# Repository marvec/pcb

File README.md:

pcb
===

Circuit boards for KiCAD

relay-board - I2C based relay board that can control 8 AC outputs (250V 10A)

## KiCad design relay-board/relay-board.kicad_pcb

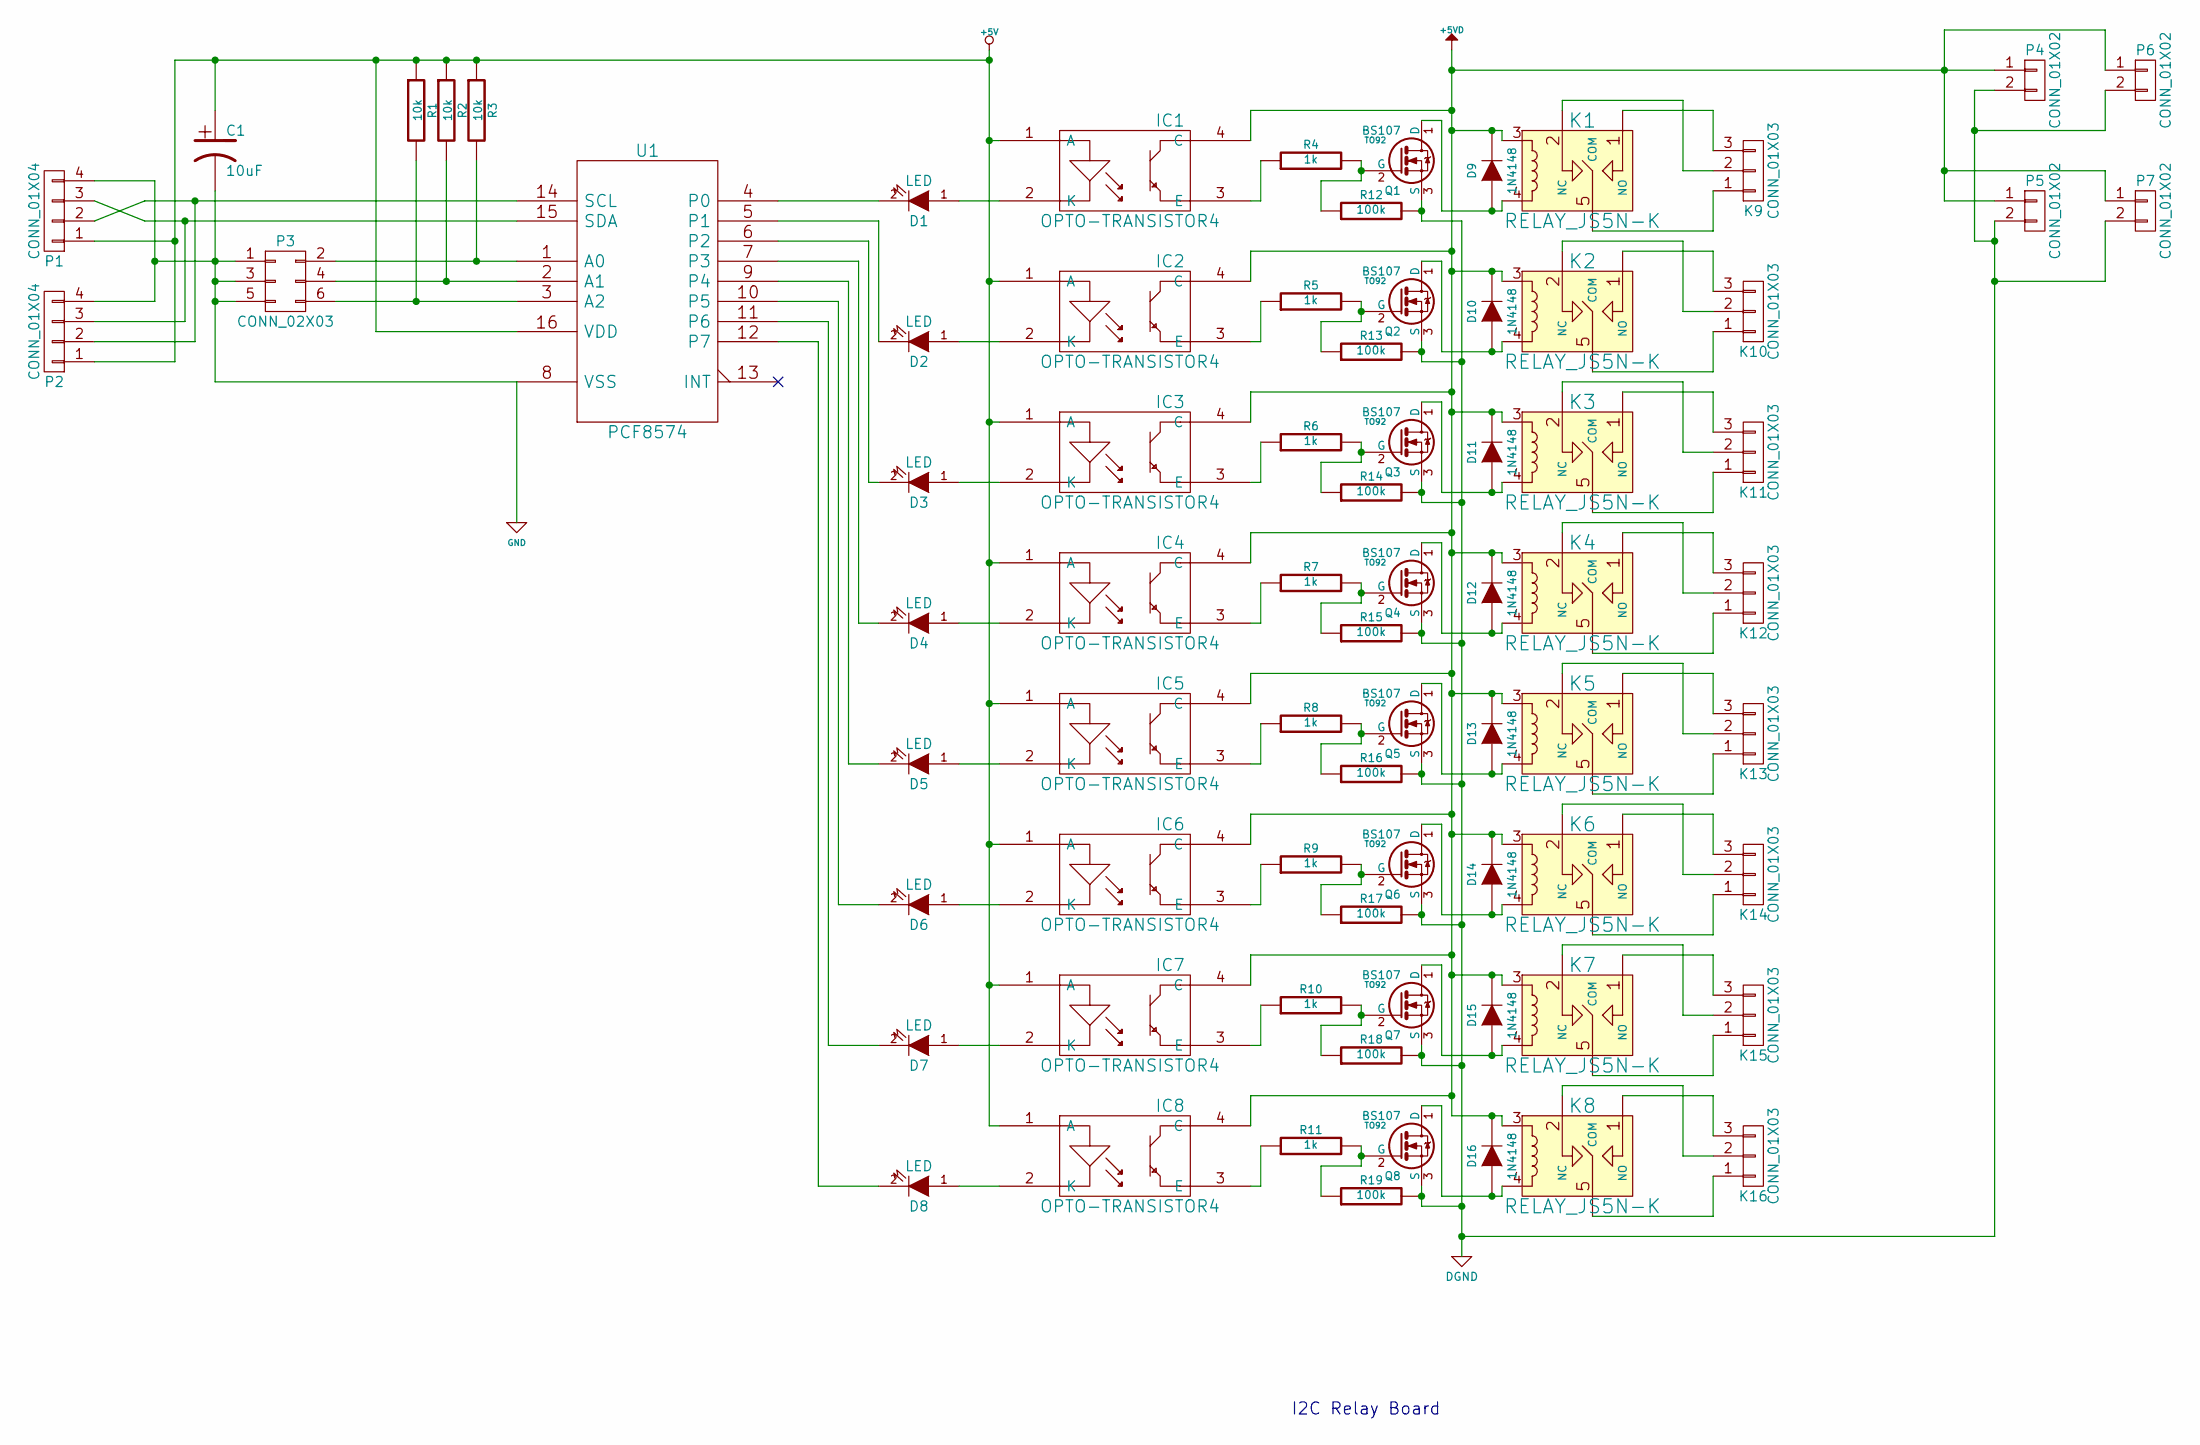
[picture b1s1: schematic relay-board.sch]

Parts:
C1: 10uF
D1, D2, D3, D4, D5, D6, D7, D8: LED
D9, D10, D11, D12, D13, D14, D15, D16: 1N4148
IC1, IC2, IC3, IC4, IC5, IC6, IC7, IC8: OPTO-TRANSISTOR4
K1, K2, K3, K4, K5, K6, K7, K8: RELAY_JS5N-K
K9, K10, K11, K12, K13, K14, K15, K16: CONN_01X03
P1, P2: CONN_01X04
P3: CONN_02X03
P4, P5, P6, P7: CONN_01X02
Q1, Q2, Q3, Q4, Q5, Q6, Q7, Q8: BS107; TO92
R1, R2, R3: 10k
R4, R5, R6, R7, R8, R9, R10, R11: 1k
R12, R13, R14, R15, R16, R17, R18, R19: 100k
U1: PCF8574

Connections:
+5V: C1.1, IC1.1 (A), IC2.1 (A), IC3.1 (A), IC4.1 (A), IC5.1 (A), IC6.1 (A), IC7.1 (A), IC8.1 (A), P1.1, P2.1, R1.1, R2.1, R3.1, U1.16 (VDD)
+5VD: D9.2 (K), D10.2 (K), D11.2 (K), D12.2 (K), D13.2 (K), D14.2 (K), D15.2 (K), D16.2 (K), IC1.4 (C), IC2.4 (C), IC3.4 (C), IC4.4 (C), IC5.4 (C), IC6.4 (C), IC7.4 (C), IC8.4 (C), K1.3, K2.3, K3.3, K4.3, K5.3, K6.3, K7.3, K8.3, P4.1, P5.1, P6.1, P7.1
DGND: P4.2, P5.2, P6.2, P7.2, Q1.3 (S), Q2.3 (S), Q3.3 (S), Q4.3 (S), Q5.3 (S), Q6.3 (S), Q7.3 (S), Q8.3 (S), R12.2, R13.2, R14.2, R15.2, R16.2, R17.2, R18.2, R19.2
GND: C1.2, P1.4, P2.4, P3.1, P3.3, P3.5, U1.8 (VSS)
unnamed: IC6.3 (E), R9.1
unnamed: IC7.3 (E), R10.1
unnamed: K7.5 (COM), K15.1
unnamed: K7.2 (NC), K15.2
unnamed: K8.5 (COM), K16.1
unnamed: IC8.3 (E), R11.1
unnamed: K8.2 (NC), K16.2
unnamed: IC4.3 (E), R7.1
unnamed: K5.2 (NC), K13.2
unnamed: K5.5 (COM), K13.1
unnamed: K4.5 (COM), K12.1
unnamed: K4.2 (NC), K12.2
unnamed: IC3.3 (E), R6.1
unnamed: K6.5 (COM), K14.1
unnamed: K6.2 (NC), K14.2
unnamed: IC5.3 (E), R8.1
unnamed: K6.1 (NO), K14.3
unnamed: K5.1 (NO), K13.3
unnamed: K1.1 (NO), K9.3
unnamed: K1.2 (NC), K9.2
unnamed: K1.5 (COM), K9.1
unnamed: K2.5 (COM), K10.1
unnamed: K3.5 (COM), K11.1
unnamed: K7.1 (NO), K15.3
unnamed: K8.1 (NO), K16.3
unnamed: K3.2 (NC), K11.2
unnamed: K2.1 (NO), K10.3
unnamed: K2.2 (NC), K10.2
unnamed: K3.1 (NO), K11.3
unnamed: K4.1 (NO), K12.3
unnamed: IC2.3 (E), R5.1
unnamed: IC1.3 (E), R4.1
unnamed: D2.1 (A), IC2.2 (K)
unnamed: D3.2 (K), U1.6 (P2)
unnamed: D4.2 (K), U1.7 (P3)
unnamed: D4.1 (A), IC4.2 (K)
unnamed: D2.2 (K), U1.5 (P1)
unnamed: D6.2 (K), U1.10 (P5)
unnamed: D5.2 (K), U1.9 (P4)
unnamed: D1.2 (K), U1.4 (P0)
unnamed: P1.2, P2.2, U1.14 (SCL)
unnamed: P1.3, P2.3, U1.15 (SDA)
unnamed: D8.1 (A), IC8.2 (K)
unnamed: D3.1 (A), IC3.2 (K)
unnamed: D5.1 (A), IC5.2 (K)
unnamed: D7.2 (K), U1.11 (P6)
unnamed: D8.2 (K), U1.12 (P7)
unnamed: D6.1 (A), IC6.2 (K)
unnamed: D7.1 (A), IC7.2 (K)
unnamed: D1.1 (A), IC1.2 (K)
unnamed: Q6.2 (G), R9.2, R17.1
unnamed: Q7.2 (G), R10.2, R18.1
unnamed: Q5.2 (G), R8.2, R16.1
unnamed: D10.1 (A), K2.4, Q2.1 (D)
unnamed: D11.1 (A), K3.4, Q3.1 (D)
unnamed: D12.1 (A), K4.4, Q4.1 (D)
unnamed: D13.1 (A), K5.4, Q5.1 (D)
unnamed: D14.1 (A), K6.4, Q6.1 (D)
unnamed: D15.1 (A), K7.4, Q7.1 (D)
unnamed: D16.1 (A), K8.4, Q8.1 (D)
unnamed: Q8.2 (G), R11.2, R19.1
unnamed: D9.1 (A), K1.4, Q1.1 (D)
unnamed: Q1.2 (G), R4.2, R12.1
unnamed: Q3.2 (G), R6.2, R14.1
unnamed: Q4.2 (G), R7.2, R15.1
unnamed: Q2.2 (G), R5.2, R13.1
unnamed: P3.6, R1.2, U1.3 (A2)
unnamed: P3.2, R3.2, U1.1 (A0)
unnamed: P3.4, R2.2, U1.2 (A1)

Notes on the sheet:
I2C Relay Board

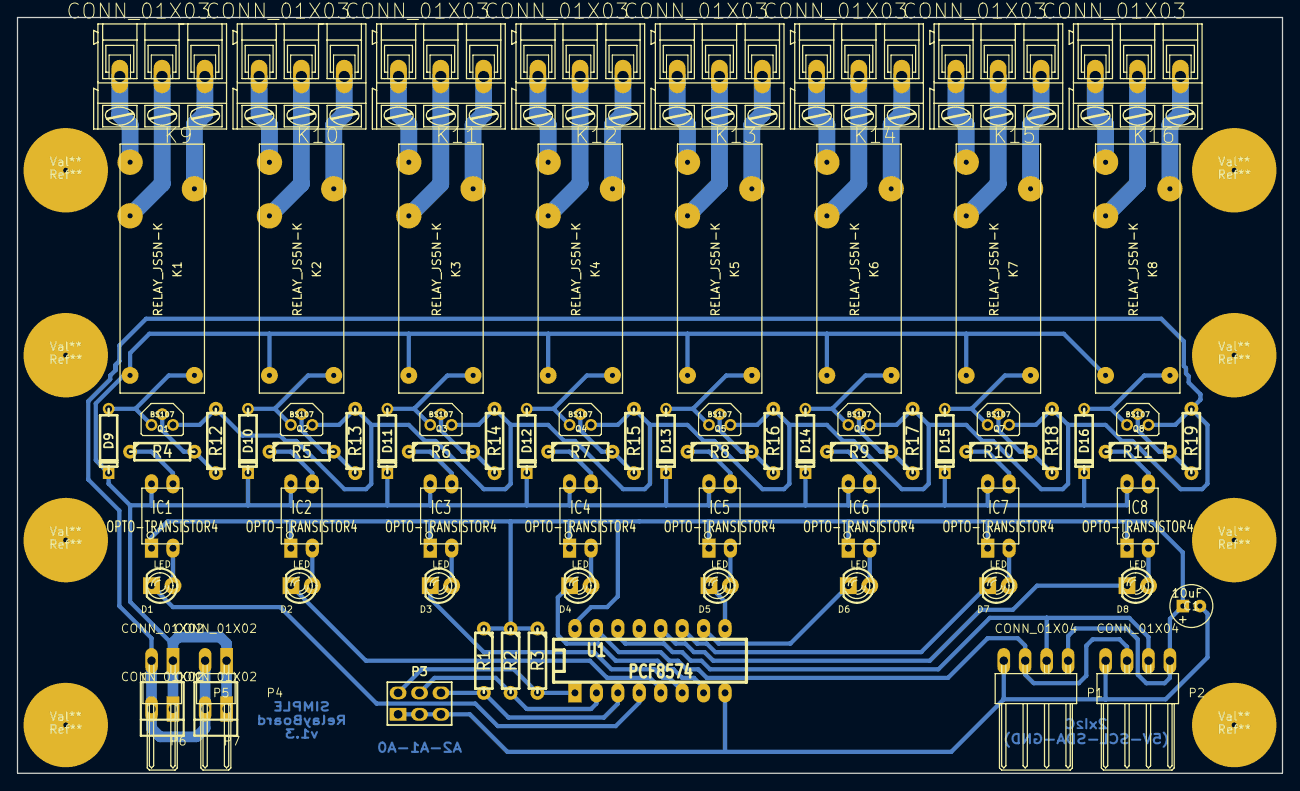
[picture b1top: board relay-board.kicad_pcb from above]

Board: 2 copper layers, 149.9 x 89.5 mm, 84 parts (0 on the bottom side), 73 nets.

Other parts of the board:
Ref**: Val**; screw-pad
Ref**#2, Ref**#3, Ref**#4, Ref**#5, Ref**#6, Ref**#7, Ref**#8: Val**; screw-pad

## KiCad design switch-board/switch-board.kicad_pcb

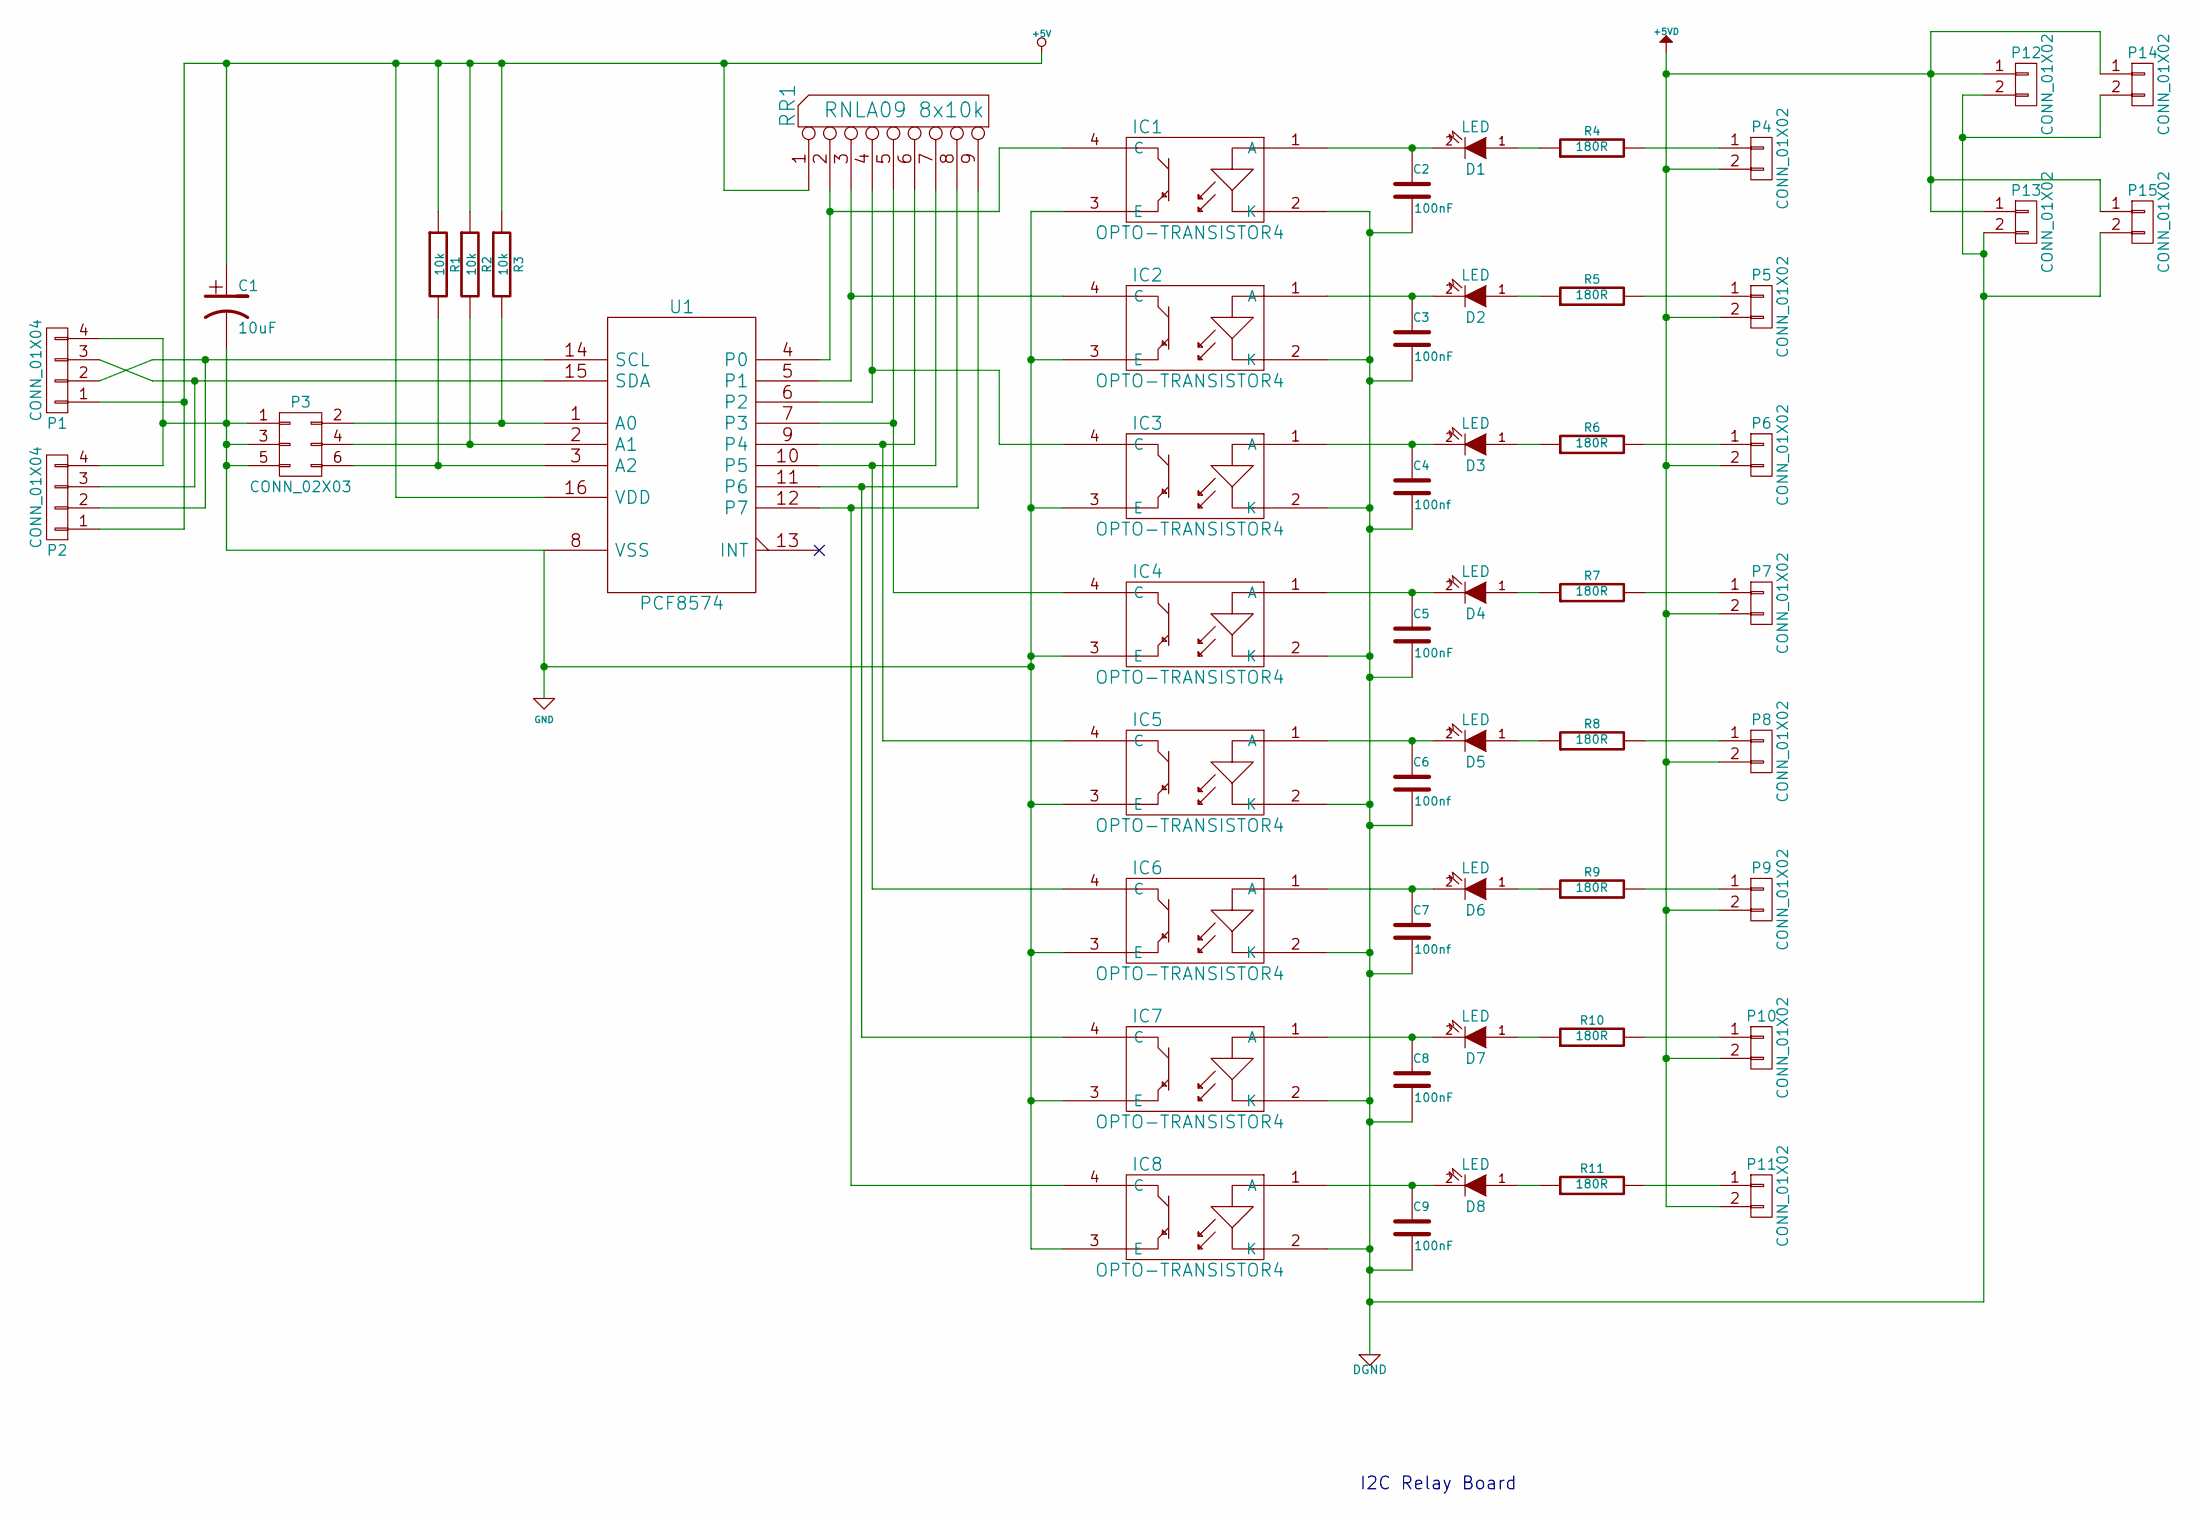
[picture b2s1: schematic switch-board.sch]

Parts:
C1: 10uF
C2, C3, C5, C8, C9: 100nF
C4, C6, C7: 100nf
D1, D2, D3, D4, D5, D6, D7, D8: LED
IC1, IC2, IC3, IC4, IC5, IC6, IC7, IC8: OPTO-TRANSISTOR4
P1, P2: CONN_01X04
P3: CONN_02X03
P4, P5, P6, P7, P8, P9, P10, P11, P12, P13, P14, P15: CONN_01X02
R1, R2, R3: 10k
R4, R5, R6, R7, R8, R9, R10, R11: 180R
RR1: RNLA09 8x10k
U1: PCF8574

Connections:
+5V: C1.1, P1.1, P2.1, R1.1, R2.1, R3.1, RR1.1 (COM), U1.16 (VDD)
+5VD: P4.2, P5.2, P6.2, P7.2, P8.2, P9.2, P10.2, P11.2, P12.1, P13.1, P14.1, P15.1
DGND: C2.2, C3.2, C4.2, C5.2, C6.2, C7.2, C8.2, C9.2, IC1.2 (K), IC2.2 (K), IC3.2 (K), IC4.2 (K), IC5.2 (K), IC6.2 (K), IC7.2 (K), IC8.2 (K), P12.2, P13.2, P14.2, P15.2
GND: C1.2, IC1.3 (E), IC2.3 (E), IC3.3 (E), IC4.3 (E), IC5.3 (E), IC6.3 (E), IC7.3 (E), IC8.3 (E), P1.4, P2.4, P3.1, P3.3, P3.5, U1.8 (VSS)
unnamed: D7.1 (A), R10.1
unnamed: P9.1, R9.2
unnamed: P8.1, R8.2
unnamed: P7.1, R7.2
unnamed: P6.1, R6.2
unnamed: P5.1, R5.2
unnamed: P4.1, R4.2
unnamed: D1.1 (A), R4.1
unnamed: P10.1, R10.2
unnamed: P3.4, R2.2, U1.2 (A1)
unnamed: P3.6, R1.2, U1.3 (A2)
unnamed: P3.2, R3.2, U1.1 (A0)
unnamed: P11.1, R11.2
unnamed: D8.1 (A), R11.1
unnamed: IC4.4 (C), RR1.5, U1.7 (P3)
unnamed: IC8.4 (C), RR1.9, U1.12 (P7)
unnamed: IC7.4 (C), RR1.8, U1.11 (P6)
unnamed: IC6.4 (C), RR1.7, U1.10 (P5)
unnamed: IC5.4 (C), RR1.6, U1.9 (P4)
unnamed: IC3.4 (C), RR1.4, U1.6 (P2)
unnamed: IC2.4 (C), RR1.3, U1.5 (P1)
unnamed: IC1.4 (C), RR1.2, U1.4 (P0)
unnamed: D5.1 (A), R8.1
unnamed: D4.1 (A), R7.1
unnamed: D6.1 (A), R9.1
unnamed: D2.1 (A), R5.1
unnamed: D3.1 (A), R6.1
unnamed: P1.3, P2.3, U1.15 (SDA)
unnamed: P1.2, P2.2, U1.14 (SCL)
unnamed: C7.1, D6.2 (K), IC6.1 (A)
unnamed: C8.1, D7.2 (K), IC7.1 (A)
unnamed: C9.1, D8.2 (K), IC8.1 (A)
unnamed: C2.1, D1.2 (K), IC1.1 (A)
unnamed: C3.1, D2.2 (K), IC2.1 (A)
unnamed: C4.1, D3.2 (K), IC3.1 (A)
unnamed: C5.1, D4.2 (K), IC4.1 (A)
unnamed: C6.1, D5.2 (K), IC5.1 (A)

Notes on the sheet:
I2C Relay Board

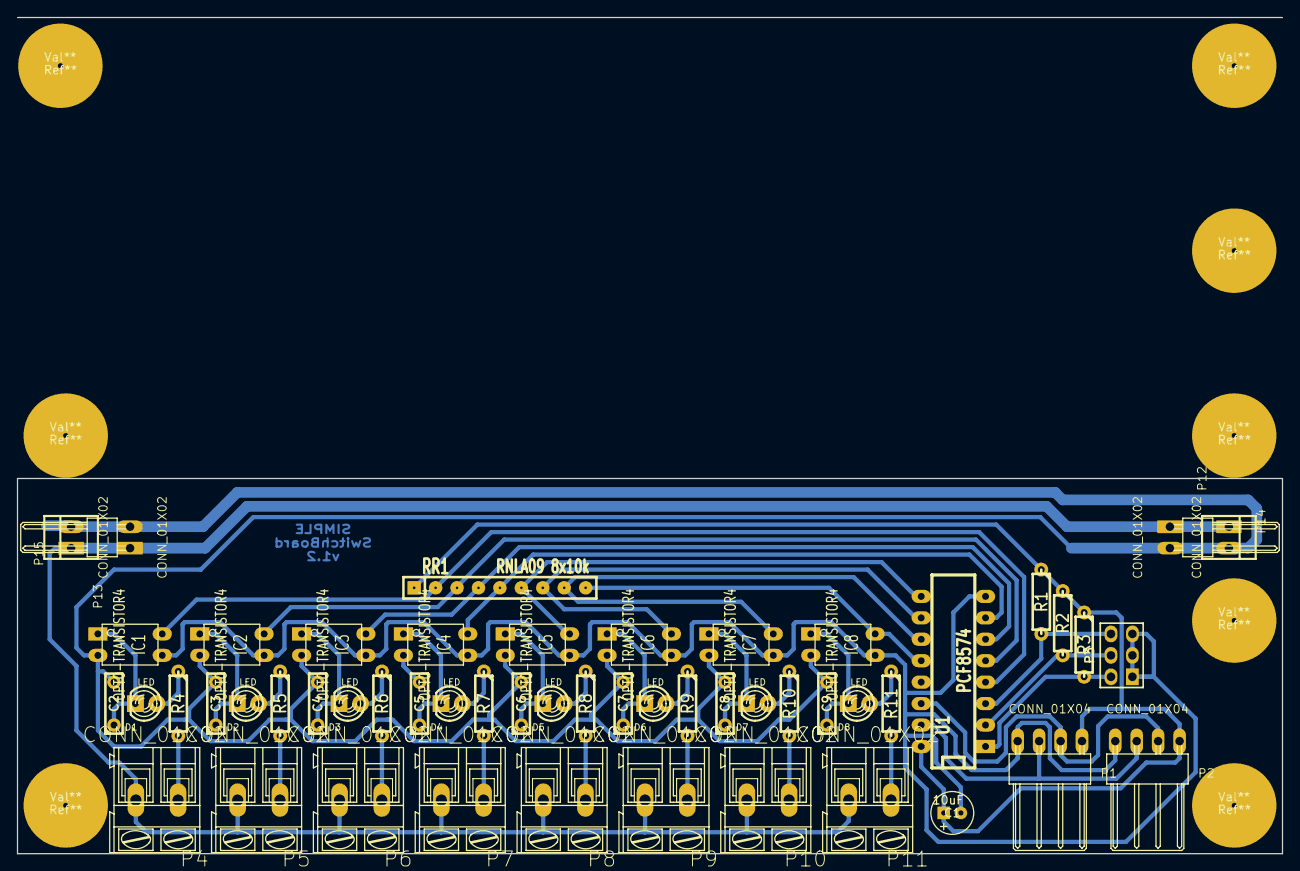
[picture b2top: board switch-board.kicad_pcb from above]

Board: 2 copper layers, 149.9 x 99.1 mm, 61 parts (0 on the bottom side), 41 nets.

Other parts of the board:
Ref**: Val**; screw-pad
Ref**#2, Ref**#3, Ref**#4, Ref**#5, Ref**#6, Ref**#7, Ref**#8: Val**; screw-pad

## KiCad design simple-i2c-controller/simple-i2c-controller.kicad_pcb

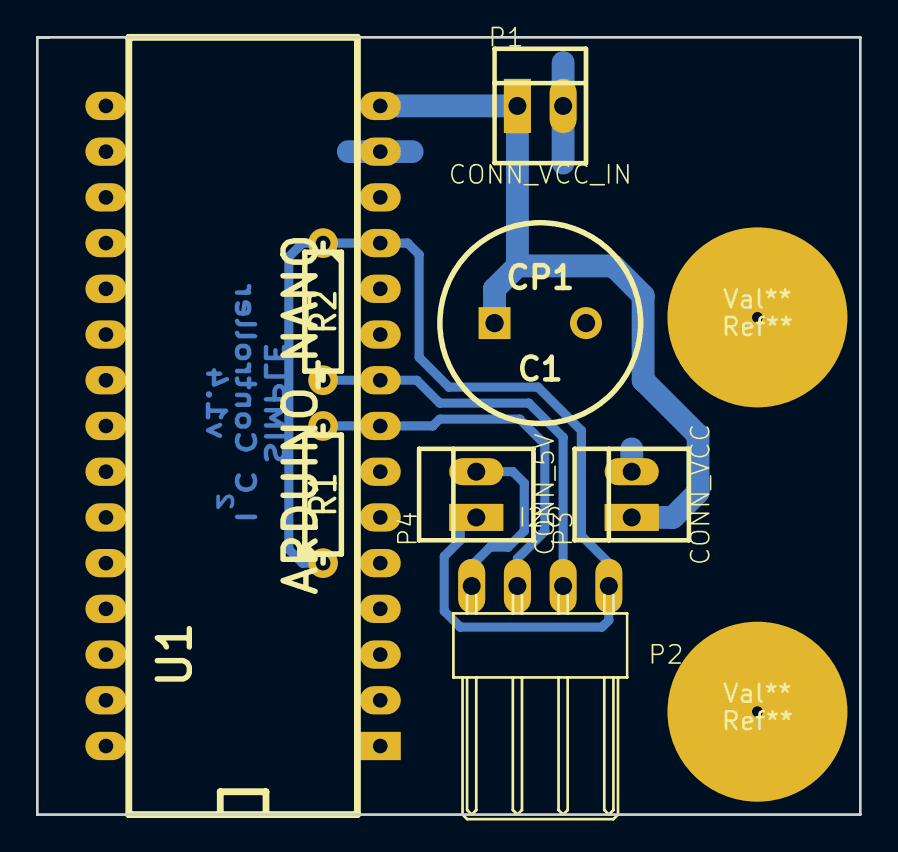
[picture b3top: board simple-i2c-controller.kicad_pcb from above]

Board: 2 copper layers, 45.7 x 43.2 mm, 10 parts (0 on the bottom side), 5 nets.

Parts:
C1: CP1; C2V10
P1: CONN_VCC_IN; PINHEAD1-2-UP
P2: I2C; PINHEAD1-4-90
P3: CONN_VCC; PINHEAD1-2-UP
P4: CONN_5V; PINHEAD1-2-UP
R1, R2: 10k; R3-LARGE_PADS
Ref**: Val**; pad
Ref**#2: Val**; pad
U1: ARDUINO_NANO; arduino_nano

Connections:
+5V: P2.1, P4.1, R1.1, R2.1, U1.12
GND: C1.2, P1.2, P2.4, P3.2, P4.2, U1.14, U1.19
unnamed: P2.3, R1.2, U1.8
unnamed: P2.2, R2.2, U1.9
VCC: C1.1, P1.1, P3.1, U1.15

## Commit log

2014-12-07 added relay board
2015-04-12 [relay-board] Updated schema, created PCB and added libraries with modules.
2015-04-13 [relay-board] Tweaked label.
2015-04-13 [simple-i2c-controller] Created project for SIMPLE I2C Controller using Arduino Nano.
2015-04-13 [SIMPLE] Created part and module libraries for SIMPLE projects.
2015-04-13 [relay-board] Updated project file for libraries.
2015-04-25 added switches board
2015-04-25 completed switches board scheme
2015-04-29 [switch-board] Created PCB.
2015-04-29 [simple-i2c-controller]
2015-04-29 [relay-board] Updated and polished PCB (to version 1.1)
2015-05-06 [simple-i2c-controller] Added pull-up resistors to i2c bus.
2015-05-06 [switch-board] Updated PCB to look better.
2015-05-13 [relay-board] Screw holes enlarged and rearranged.
2015-05-13 [simple-i2c-controller] Screw holes enlarged and rearranged.
2015-05-13 [switch-board] Screw holes enlarged and rearranged.
2015-05-13 [simple-i2c-controller] Fixed a glitch in PCB.
2015-05-13 [relay-board] Updated PCB.
2015-05-13 [switch-board] Updated PCB.
2015-05-13 [relay-board] Polished PCB.
